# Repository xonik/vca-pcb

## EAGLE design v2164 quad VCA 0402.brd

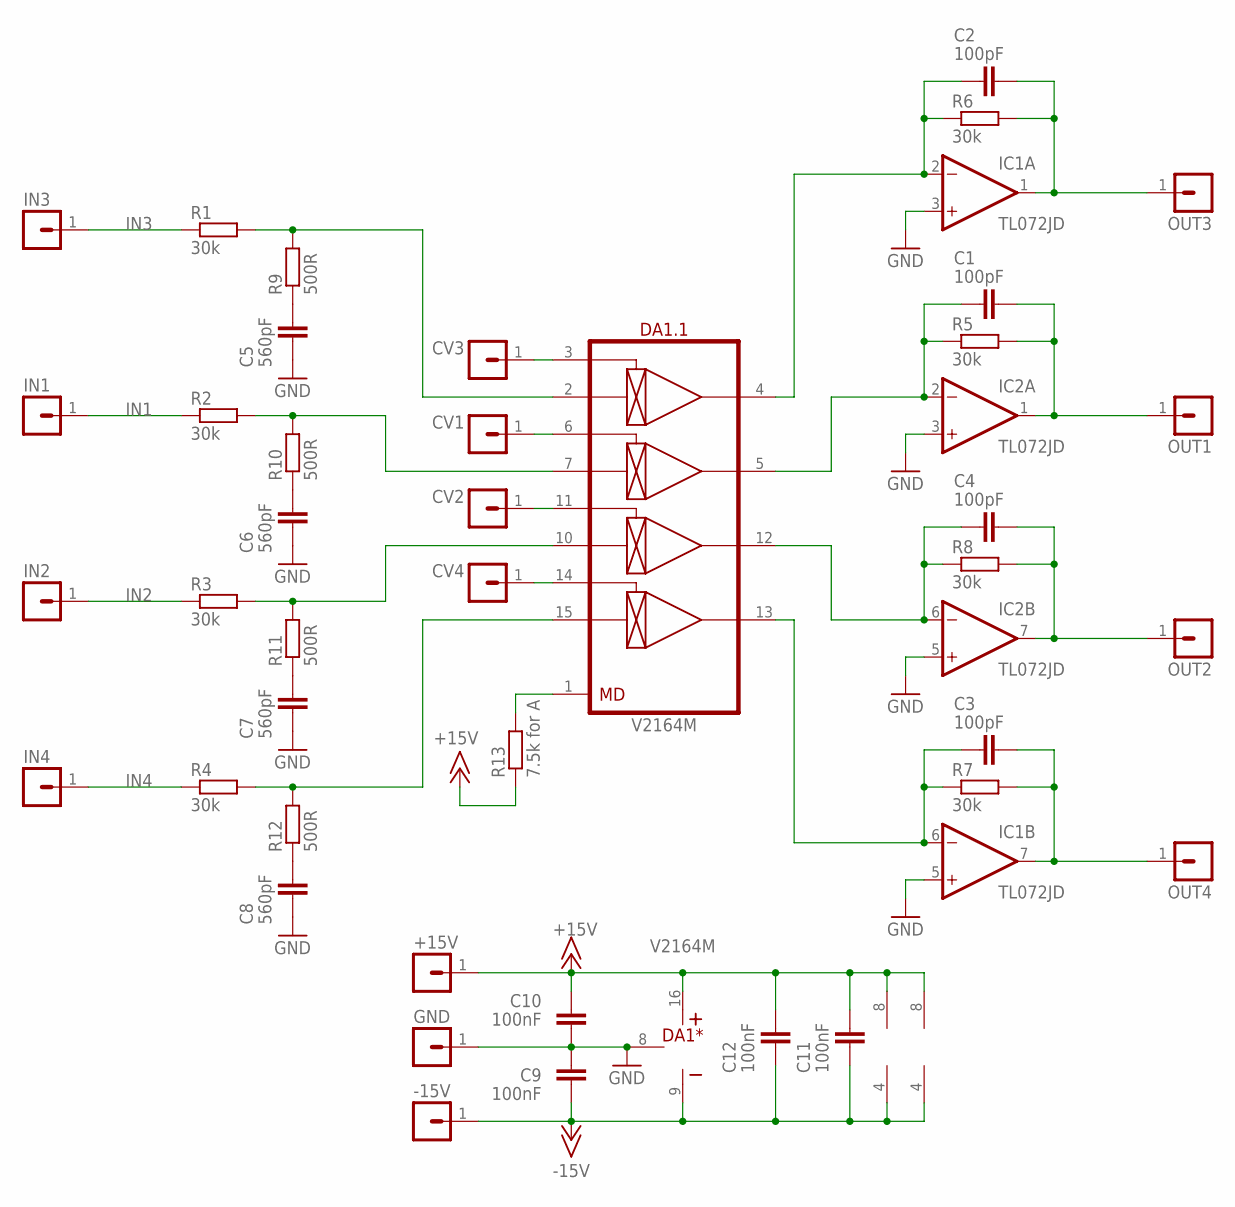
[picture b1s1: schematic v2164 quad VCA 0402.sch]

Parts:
+15V: MA01-1JN; MA01N-1J
-15V: MA01-1JN; MA01N-1J
C1, C2, C3, C4: 100pF; C0402
C5, C6, C7, C8: 560pF; C0603
C9, C10, C11, C12: 100nF; C0402
CV1, CV2, CV3, CV4: MA01-1JN; MA01N-1J
DA1: V2164M; SO-16
GND: MA01-1JN; MA01N-1J
IC1, IC2: TL072JD; SO08J
IN1, IN2, IN3, IN4: MA01-1JN; MA01N-1J
OUT1, OUT2, OUT3, OUT4: MA01-1JN; MA01N-1J
R1, R2, R3, R4, R5, R6, R7, R8: 30k; R0402
R9, R10, R11, R12: 500R; R0402
R13: 7.5k for A; R0402

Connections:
+15V: +15V.1, C10.2, C11.2, C12.2, DA1.16 (V+), IC1.8 (V+), IC2.8 (V+), R13.1
-15V: -15V.1, C9.1, C11.1, C12.1, DA1.9 (V-), IC1.4 (V-), IC2.4 (V-); also elsewhere on the board
CV1: CV1.1, DA1.6 (CV2)
CV2: CV2.1, DA1.11 (CV3)
CV3: CV3.1, DA1.3 (CV1)
CV4: CV4.1, DA1.14 (CV4)
GND: C5.1, C6.1, C7.1, C8.1, C9.2, C10.1, DA1.8 (GND), GND.1, IC1.3 (+IN), IC1.5 (+IN), IC2.3 (+IN), IC2.5 (+IN); also elsewhere on the board
IN1: IN1.1, R2.1
IN2: IN2.1, R3.1
IN3: IN3.1, R1.1
IN4: IN4.1, R4.1
unnamed: C4.1, DA1.12 (OUT3), IC2.6 (-IN), R8.1
unnamed: DA1.1 (MD), R13.2
unnamed: C3.1, DA1.13 (OUT4), IC1.6 (-IN), R7.1
unnamed: C2.1, DA1.4 (OUT1), IC1.2 (-IN), R6.1
unnamed: C1.1, DA1.5 (OUT2), IC2.2 (-IN), R5.1
unnamed: C5.2, R9.1
unnamed: C6.2, R10.1
unnamed: C7.2, R11.1
unnamed: C8.2, R12.1
unnamed: DA1.2 (IN1), R1.2, R9.2
unnamed: DA1.7 (IN2), R2.2, R10.2
unnamed: DA1.10 (IN3), R3.2, R11.2
unnamed: DA1.15 (IN4), R4.2, R12.2
OUT1: C1.2, IC2.1 (OUT), OUT1.1, R5.2
OUT2: C4.2, IC2.7 (OUT), OUT2.1, R8.2
OUT3: C2.2, IC1.1 (OUT), OUT3.1, R6.2
OUT4: C3.2, IC1.7 (OUT), OUT4.1, R7.2

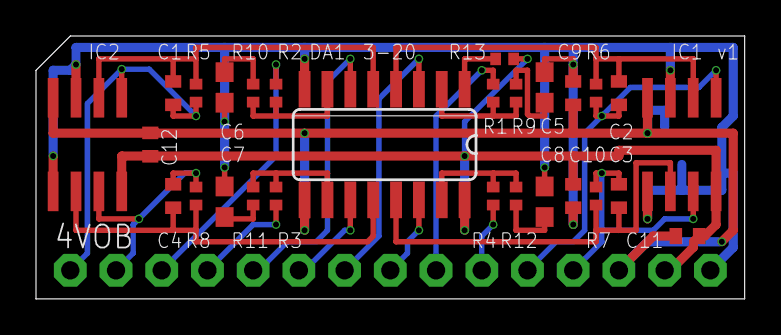
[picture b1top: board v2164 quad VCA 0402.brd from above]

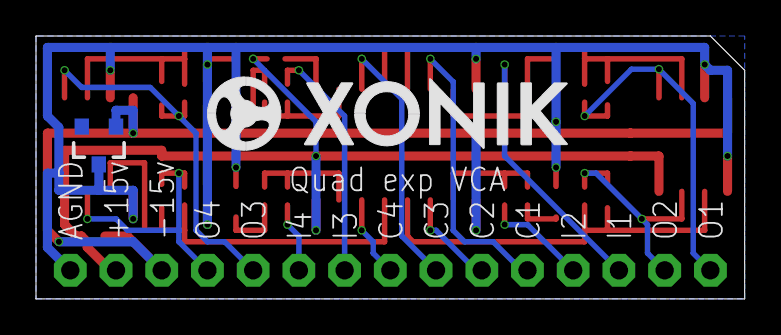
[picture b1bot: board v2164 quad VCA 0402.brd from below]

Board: 2 copper layers, 39.4 x 14.6 mm, 45 parts (2 on the bottom side), 28 nets.

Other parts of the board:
Q1: BA854SW; SOT23-3J
U$1: XONIK_LOGO_20

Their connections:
-15V: Q1.1; also elsewhere on the board
GND: Q1.3; also elsewhere on the board

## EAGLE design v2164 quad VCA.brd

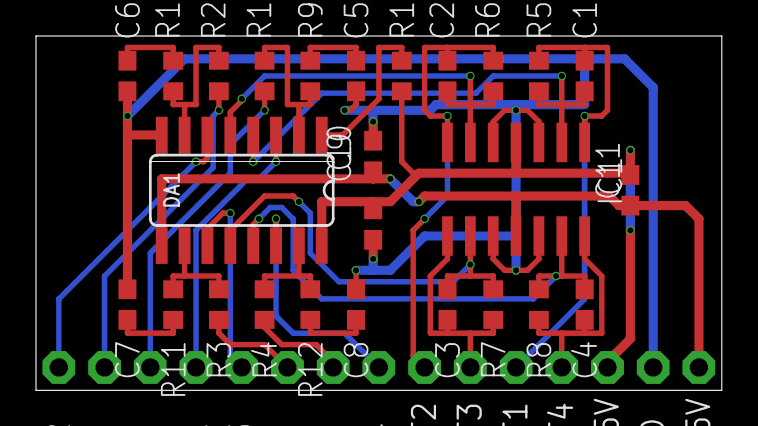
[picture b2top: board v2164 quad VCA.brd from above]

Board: 2 copper layers, 38.1 x 19.7 mm, 41 parts (0 on the bottom side), 28 nets.

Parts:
+15V: MA01N-1J
-15V: MA01N-1J
C1, C2, C3, C4: 100pF; C0603
C5, C6, C7, C8: 560pF; C0603
C9, C10, C11: 100nF; C0603
CV1, CV2, CV3, CV4: MA01N-1J
DA1: V2164M; SO-16
GND: MA01N-1J
IC1: TL074JD; SO14J
IN1, IN2, IN3, IN4: MA01N-1J
OUT1, OUT2, OUT3, OUT4: MA01N-1J
R1, R2, R3, R4, R5, R6, R7, R8: 30k; R0603
R9, R10, R11, R12: 500R; R0603
R13: 7.5k for A; R0603

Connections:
+15V: +15V.1, C10.2, C11.2, DA1.16, IC1.4, R13.1
-15V: -15V.1, C9.1, C11.1, DA1.9, IC1.11
CV1: CV1.1, DA1.3
CV2: CV2.1, DA1.6
CV3: CV3.1, DA1.11
CV4: CV4.1, DA1.14
GND: C5.1, C6.1, C7.1, C8.1, C9.2, C10.1, DA1.8, GND.1, IC1.3, IC1.5, IC1.10, IC1.12
IN1: IN1.1, R1.1
IN2: IN2.1, R2.1
IN3: IN3.1, R3.1
IN4: IN4.1, R4.1
unnamed: C4.1, DA1.13, IC1.13, R8.1
unnamed: DA1.1, R13.2
unnamed: C3.1, DA1.12, IC1.9, R7.1
unnamed: C2.1, DA1.5, IC1.6, R6.1
unnamed: C1.1, DA1.4, IC1.2, R5.1
unnamed: C5.2, R9.1
unnamed: C6.2, R10.1
unnamed: C7.2, R11.1
unnamed: C8.2, R12.1
unnamed: DA1.2, R1.2, R9.2
unnamed: DA1.7, R2.2, R10.2
unnamed: DA1.10, R3.2, R11.2
unnamed: DA1.15, R4.2, R12.2
OUT1: C1.2, IC1.1, OUT1.1, R5.2
OUT2: C2.2, IC1.7, OUT2.1, R6.2
OUT3: C3.2, IC1.8, OUT3.1, R7.2
OUT4: C4.2, IC1.14, OUT4.1, R8.2
